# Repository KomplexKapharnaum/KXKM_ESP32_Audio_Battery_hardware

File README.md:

# KXKM_ESP32_Audio_Battery_hardware

## Overview
Hardware workspace for the KXKM ESP32 battery + audio platform.
The repository groups KiCad design files for battery management and remote control boards.

## Installation
Prerequisites:
- KiCad 7/8 for schematic/project edits
- Git LFS is not required for the current tracked files

## Usage
Typical workflow:
1. Open the board project under `Base_board/v3.2/`.
2. Review schematic updates in `*.kicad_sch`.
3. Export manufacturing artifacts (Gerber/BOM) from KiCad when needed.

## Architecture
Main areas:
- `Base_board/`: battery management board revisions
- `Audio_board/`: audio-related board files
- `Remote_control_board/`: remote control board symbols/project config

## Testing & Quality
Recommended checks before commit:
- KiCad ERC/DRC on edited projects
- Diff review on `.kicad_sch`/`.kicad_pro` changes
- Ensure no local artifacts are tracked (`.DS_Store`, `*-backups/*.zip`)

## Performance & Optimization
Optimization focus:
- Keep schematic commits isolated from hygiene/meta commits
- Reduce noisy diffs by excluding generated/local backup files

## Security
Security notes:
- Avoid committing private manufacturing or supplier credentials
- Keep BOM/vendor metadata reviewable in plain text when possible

## Roadmap
Near-term:
- Finalize battery board v3.2 review cycle
- Validate remote control symbol table consistency

<!-- CHANTIER:AUDIT START -->
## Audit & Execution Plan (2026-03-10)

### Snapshot
- Priority: `P2`
- Tech profile: `other`
- Workflows: `yes`
- Tests: `yes`
- Debt markers: `0`
- Source files: `0`

### Corrections Prioritaires
- [ ] Optimisation ciblée perf/maintenabilité
- [ ] Ajouter/fiabiliser les commandes de vérification automatiques.
- [ ] Clore les points bloquants avant optimisation avancée.

### Optimisation
- [ ] Identifier le hotspot principal et mesurer avant/après.
- [ ] Réduire la complexité des modules les plus touchés.

### Mémoire chantier
- Control plane: `/Users/electron/.codex/memories/electron_rare_chantier`
- Repo card: `/Users/electron/.codex/memories/electron_rare_chantier/REPOS/KXKM_ESP32_Audio_Battery_hardware.md`

<!-- CHANTIER:AUDIT END -->

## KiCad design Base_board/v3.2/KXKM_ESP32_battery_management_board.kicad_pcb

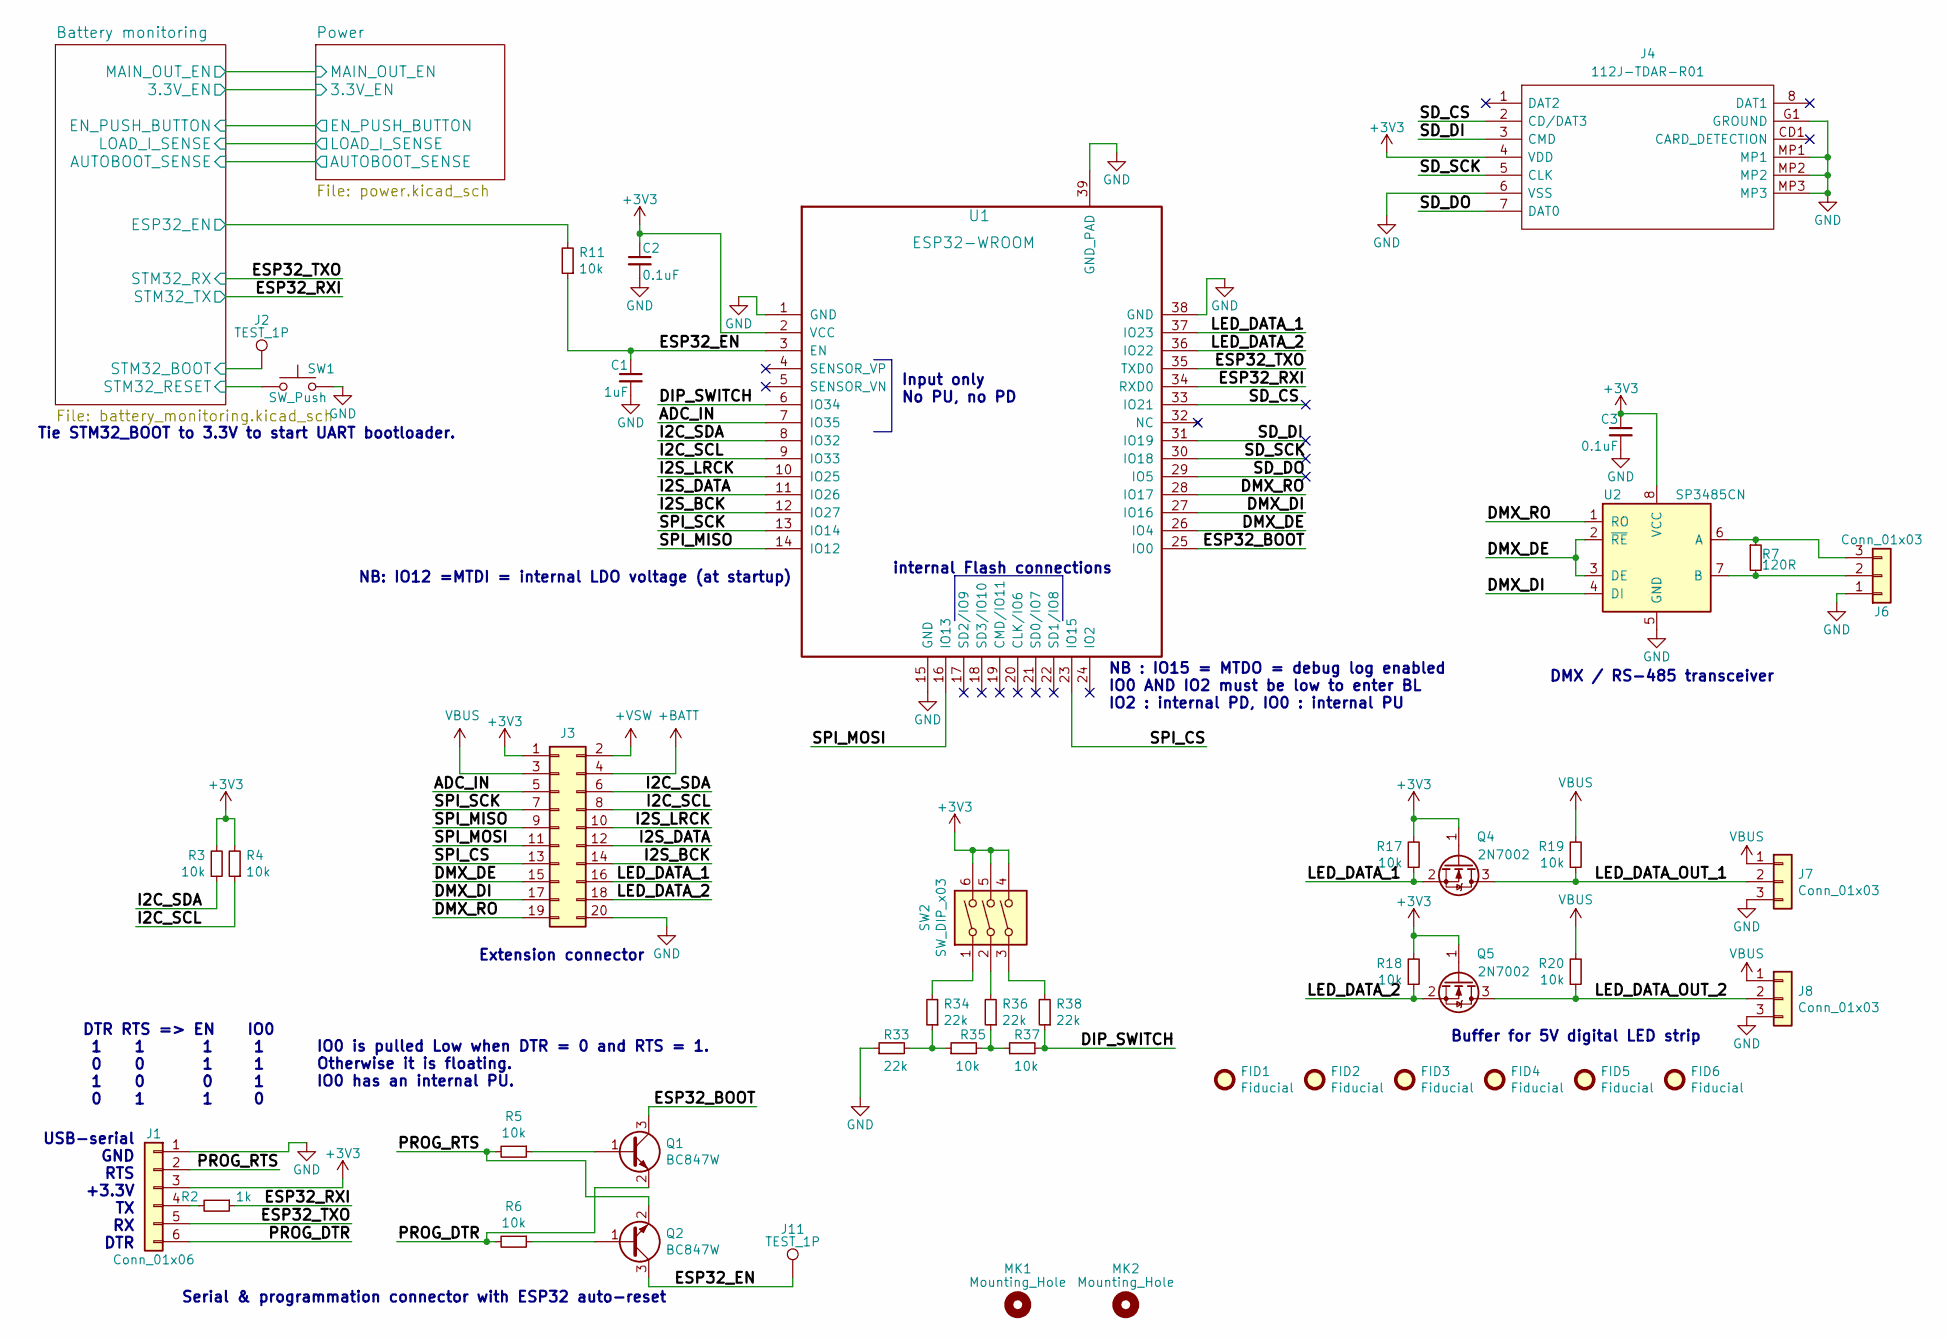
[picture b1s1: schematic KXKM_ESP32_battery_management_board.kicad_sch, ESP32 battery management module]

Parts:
C1: 1uF; C_0603_1608Metric; LCSC C15849
C2, C3: 0.1uF; C_0603_1608Metric; LCSC C14663
FID1, FID2, FID3, FID4, FID5, FID6: Fiducial; Fiducial_0.5mm_Mask1mm
J1: Conn_01x06; PinHeader_1x06_P2.54mm_Vertical
J2, J11: TEST_1P; TestPoint_Pad_D1.5mm
J3: Conn_02x10_Odd_Even; PinSocket_2x10_P2.54mm_Vertical_SMD
J4: 112J-TDAR-R01; 112JTDARR01; Manufacturer_Part_Number 112J-TDAR-R01
J6: Conn_01x03; PinHeader_1x03_P2.54mm_Vertical
J7, J8: Conn_01x03; JST_EH_B3B-EH-A_1x03_P2.50mm_Vertical
MK1, MK2: Mounting_Hole; MountingHole_3.2mm_M3
Q1, Q2: BC847W; SOT-323_SC-70; LCSC C130418
Q4, Q5: 2N7002; SOT-23; LCSC C8545
R2: 1k; R_0603_1608Metric; LCSC C21190
R3, R4, R5, R6, R11, R17, R18, R19, R20, R35, R37: 10k; R_0603_1608Metric; LCSC C25804
R7: 120R; R_0603_1608Metric; LCSC C114681
R33, R34, R36, R38: 22k; R_0603_1608Metric; LCSC C31850
SW1: SW_Push; SW_SPST_KMR2; LCSC C128941
SW2: SW_DIP_x03; SW_DIP_SPSTx03_Piano_CTS_Series194-3MSTN_W7.62mm_P2.54mm; LCSC C319070
U1: ESP32-WROOM; ESP32-WROOM-32U; LCSC C529580
U2: SP3485CN; SOIC-8_3.9x4.9mm_P1.27mm; LCSC C668205

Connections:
+3V3: C2.1, C3.1, J1.3, J3.1, J4.4 (VDD), Q4.1 (G), Q5.1 (G), R3.2, R4.2, R17.2, R18.2, SW2.4, SW2.5, SW2.6, U1.2 (VCC), U2.8 (VCC); also elsewhere on the board
+BATT: J3.4; also elsewhere on the board
+VSW: J3.2; also elsewhere on the board
/ADC_IN: J3.5, U1.7 (IO35)
/Battery monitoring/ESP32_EN: R11.2; also elsewhere on the board
/Battery monitoring/STM32_BOOT: J2.1; also elsewhere on the board
/Battery monitoring/STM32_RST: SW1.1; also elsewhere on the board
/DIP_SWITCH: R37.2, R38.1, U1.6 (IO34)
/DMX_DE: J3.15, U1.26 (IO4), U2.2 (~RE), U2.3 (DE)
/DMX_DI: J3.17, U1.27 (IO16), U2.4 (DI)
/DMX_RO: J3.19, U1.28 (IO17), U2.1 (RO)
/ESP32_BOOT: Q1.3 (C), U1.25 (IO0)
/ESP32_EN: C1.1, J11.1, Q2.3 (C), R11.1, U1.3 (EN)
/ESP32_RXI: R2.1, U1.34 (RXD0); also elsewhere on the board
/ESP32_TXO: J1.5, U1.35 (TXD0); also elsewhere on the board
/I2C_SCL: J3.8, R4.1, U1.9 (IO33)
/I2C_SDA: J3.6, R3.1, U1.8 (IO32)
/I2S_BCK: J3.14, U1.12 (IO27)
/I2S_DATA: J3.12, U1.11 (IO26)
/I2S_LRCK: J3.10, U1.10 (IO25)
/LED_DATA_1: J3.16, Q4.2 (S), R17.1, U1.37 (IO23)
/LED_DATA_2: J3.18, Q5.2 (S), R18.1, U1.36 (IO22)
/LED_DATA_OUT_1: J7.2, Q4.3 (D), R19.1
/LED_DATA_OUT_2: J8.2, Q5.3 (D), R20.1
/PROG_DTR: J1.6, Q1.2 (E), R6.2
/PROG_RTS: J1.2, Q2.2 (E), R5.2
/SD_CS: J4.2 (CD/DAT3), U1.33 (IO21)
/SD_DI: J4.3 (CMD), U1.31 (IO19)
/SD_DO: J4.7 (DAT0), U1.29 (IO5)
/SD_SCK: J4.5 (CLK), U1.30 (IO18)
/SPI_CS: J3.13, U1.23 (IO15)
/SPI_MISO: J3.9, U1.14 (IO12)
/SPI_MOSI: J3.11, U1.16 (IO13)
/SPI_SCK: J3.7, U1.13 (IO14)
GND: C1.2, C2.2, C3.2, J1.1, J3.20, J4.6 (VSS), J4.G1 (GROUND), J4.MP1, J4.MP2, J4.MP3, J6.1, J7.3, J8.3, R33.1, SW1.2, U1.1 (GND), U1.15 (GND), U1.38 (GND), U1.39 (GND_PAD), U2.5 (GND); also elsewhere on the board
unnamed: J1.4, R2.2
unnamed: J6.2, R7.2, U2.7 (B)
unnamed: J6.3, R7.1, U2.6 (A)
unnamed: Q1.1 (B), R5.1
unnamed: Q2.1 (B), R6.1
unnamed: R33.2, R34.1, R35.1
unnamed: R34.2, SW2.1
unnamed: R35.2, R36.1, R37.1
unnamed: R36.2, SW2.2
unnamed: R38.2, SW2.3
VBUS: J3.3, J7.1, J8.1, R19.2, R20.2; also elsewhere on the board

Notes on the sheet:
DMX / RS-485 transceiver
Tie STM32_BOOT to 3.3V to start UART bootloader.
DTR RTS => EN IO0 1 1 1 1 0 0 1 1 1 0 0 1 0 1 1 0
Input only No PU, no PD
Buffer for 5V digital LED strip
USB-serial GND RTS +3.3V TX RX DTR
NB : IO15 = MTDO = debug log enabled IO0 AND IO2 must be low to enter BL IO2 : internal PD, IO0 : internal PU
Serial & programmation connector with ESP32 auto-reset
IO0 is pulled Low when DTR = 0 and RTS = 1. Otherwise it is floating. IO0 has an internal PU.
NB: IO12 =MTDI = internal LDO voltage (at startup)
internal Flash connections
Extension connector

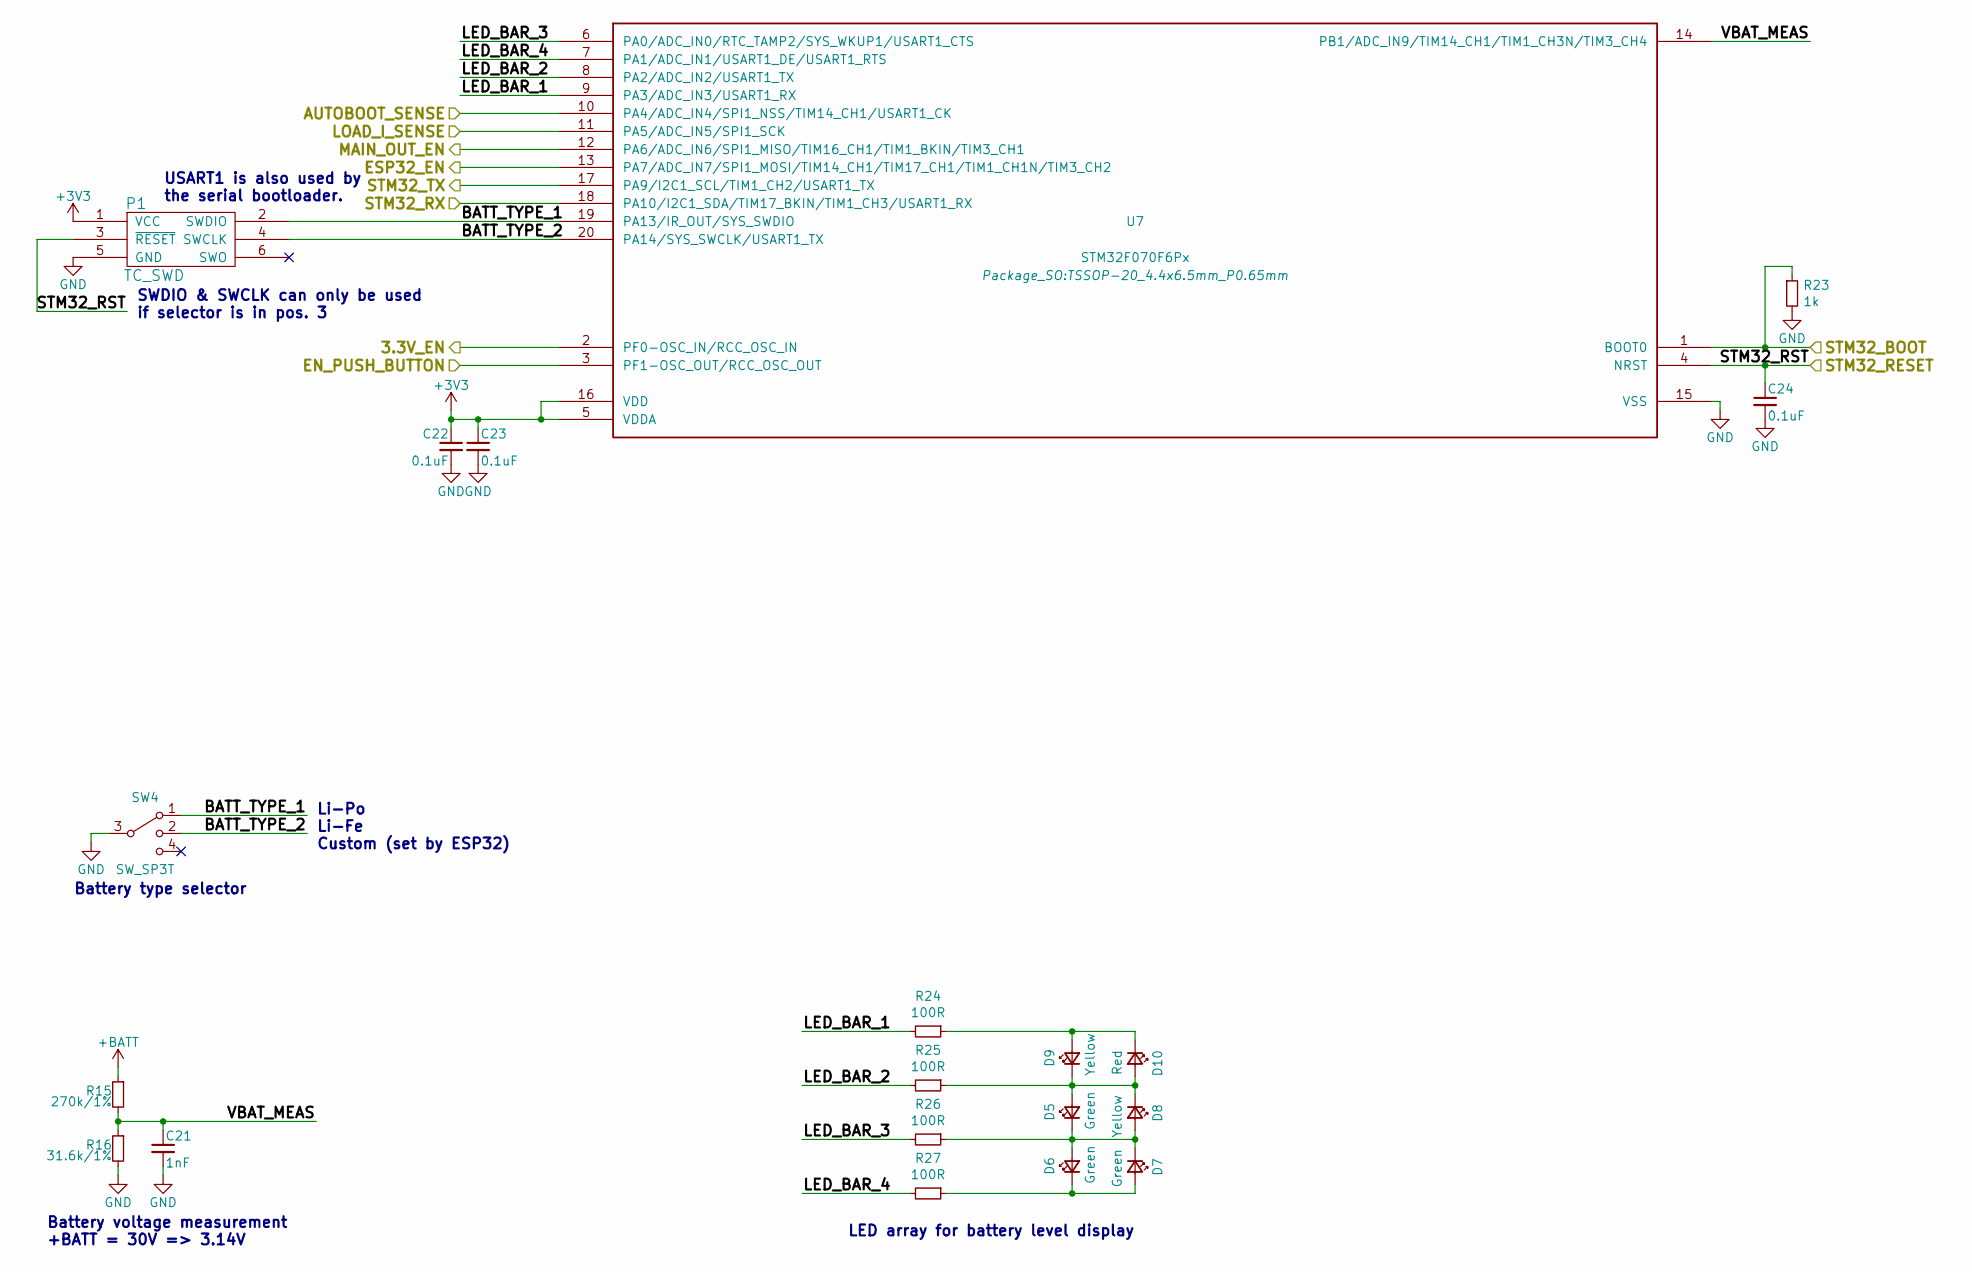
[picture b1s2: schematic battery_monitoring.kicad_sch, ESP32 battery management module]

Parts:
C21: 1nF; C_0603_1608Metric
C22, C23, C24: 0.1uF; C_0603_1608Metric; LCSC C14663
D5, D6, D7: Green; LED_0603_1608Metric; LCSC C72043
D8, D9: Yellow; LED_0603_1608Metric; LCSC C72038
D10: Red; LED_0603_1608Metric; LCSC C2286
P1: TC_SWD; Tag-Connect_TC2030-IDC-NL_2x03_P1.27mm_Vertical
R15: 270k/1%; R_0603_1608Metric; LCSC C22965
R16: 31.6k/1%; R_0603_1608Metric; LCSC C25967
R23: 1k; R_0603_1608Metric; LCSC C21190
R24, R25, R26, R27: 100R; R_0603_1608Metric; LCSC C22775
SW4: SW_SP3T; SW_SP3T_PCM13; LCSC C160878
U7: STM32F070F6Px; TSSOP-20_4.4x6.5mm_P0.65mm; LCSC C86951

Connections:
+3V3: C22.1, C23.1, P1.1 (VCC), U7.5 (VDDA), U7.16 (VDD); also elsewhere on the board
+BATT: R15.1; also elsewhere on the board
/Battery monitoring/3.3V_EN: U7.2 (PF0-OSC_IN/RCC_OSC_IN); also elsewhere on the board
/Battery monitoring/AUTOBOOT_SENSE: U7.10 (PA4/ADC_IN4/SPI1_NSS/TIM14_CH1/USART1_CK); also elsewhere on the board
/Battery monitoring/BATT_TYPE_1: P1.2 (SWDIO), SW4.1, U7.19 (PA13/IR_OUT/SYS_SWDIO)
/Battery monitoring/BATT_TYPE_2: P1.4 (SWCLK), SW4.2, U7.20 (PA14/SYS_SWCLK/USART1_TX)
/Battery monitoring/EN_PUSH_BUTTON: U7.3 (PF1-OSC_OUT/RCC_OSC_OUT); also elsewhere on the board
/Battery monitoring/ESP32_EN: U7.13 (PA7/ADC_IN7/SPI1_MOSI/TIM14_CH1/TIM17_C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); also elsewhere on the board
/Battery monitoring/LED_BAR_1: R24.2, U7.9 (PA3/ADC_IN3/USART1_RX)
/Battery monitoring/LED_BAR_2: R25.2, U7.8 (PA2/ADC_IN2/USART1_TX)
/Battery monitoring/LED_BAR_3: R26.2, U7.6 (PA0/ADC_IN0/RTC_TAMP2/SYS_WKUP1/USART1_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)
/Battery monitoring/LED_BAR_4: R27.2, U7.7 (PA1/ADC_IN1/USART1_DE/USART1_RTS)
/Battery monitoring/LOAD_I_SENSE: U7.11 (PA5/ADC_IN5/SPI1_SCK); also elsewhere on the board
/Battery monitoring/MAIN_OUT_EN: U7.12 (PA6/ADC_IN6/SPI1_MISO/TIM16_CH1/TIM1_BK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); also elsewhere on the board
/Battery monitoring/STM32_BOOT: R23.1, U7.1 (BOOT0); also elsewhere on the board
/Battery monitoring/STM32_RST: C24.1, P1.3 (~RESET), U7.4 (NRST); also elsewhere on the board
/Battery monitoring/VBAT_MEAS: C21.1, R15.2, R16.1, U7.14 (PB1/ADC_IN9/TIM14_CH1/TIM1_CH3N/TIM3_CH4)
/ESP32_RXI: U7.17 (PA9/I2C1_SCL/TIM1_CH2/USART1_TX); also elsewhere on the board
/ESP32_TXO: U7.18 (PA10/I2C1_SDA/TIM17_BKIN/TIM1_CH3/USART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); also elsewhere on the board
GND: C21.2, C22.2, C23.2, C24.2, P1.5 (GND), R16.2, R23.2, SW4.3, U7.15 (VSS); also elsewhere on the board
unnamed: D5.1 (K), D6.2 (A), D7.1 (K), D8.2 (A), R26.1
unnamed: D6.1 (K), D7.2 (A), R27.1
unnamed: D5.2 (A), D8.1 (K), D9.1 (K), D10.2 (A), R25.1
unnamed: D9.2 (A), D10.1 (K), R24.1

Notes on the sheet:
Li-Po Li-Fe Custom (set by ESP32)
Battery type selector
Battery voltage measurement +BATT = 30V => 3.14V
LED array for battery level display
SWDIO & SWCLK can only be used if selector is in pos. 3
USART1 is also used by the serial bootloader.

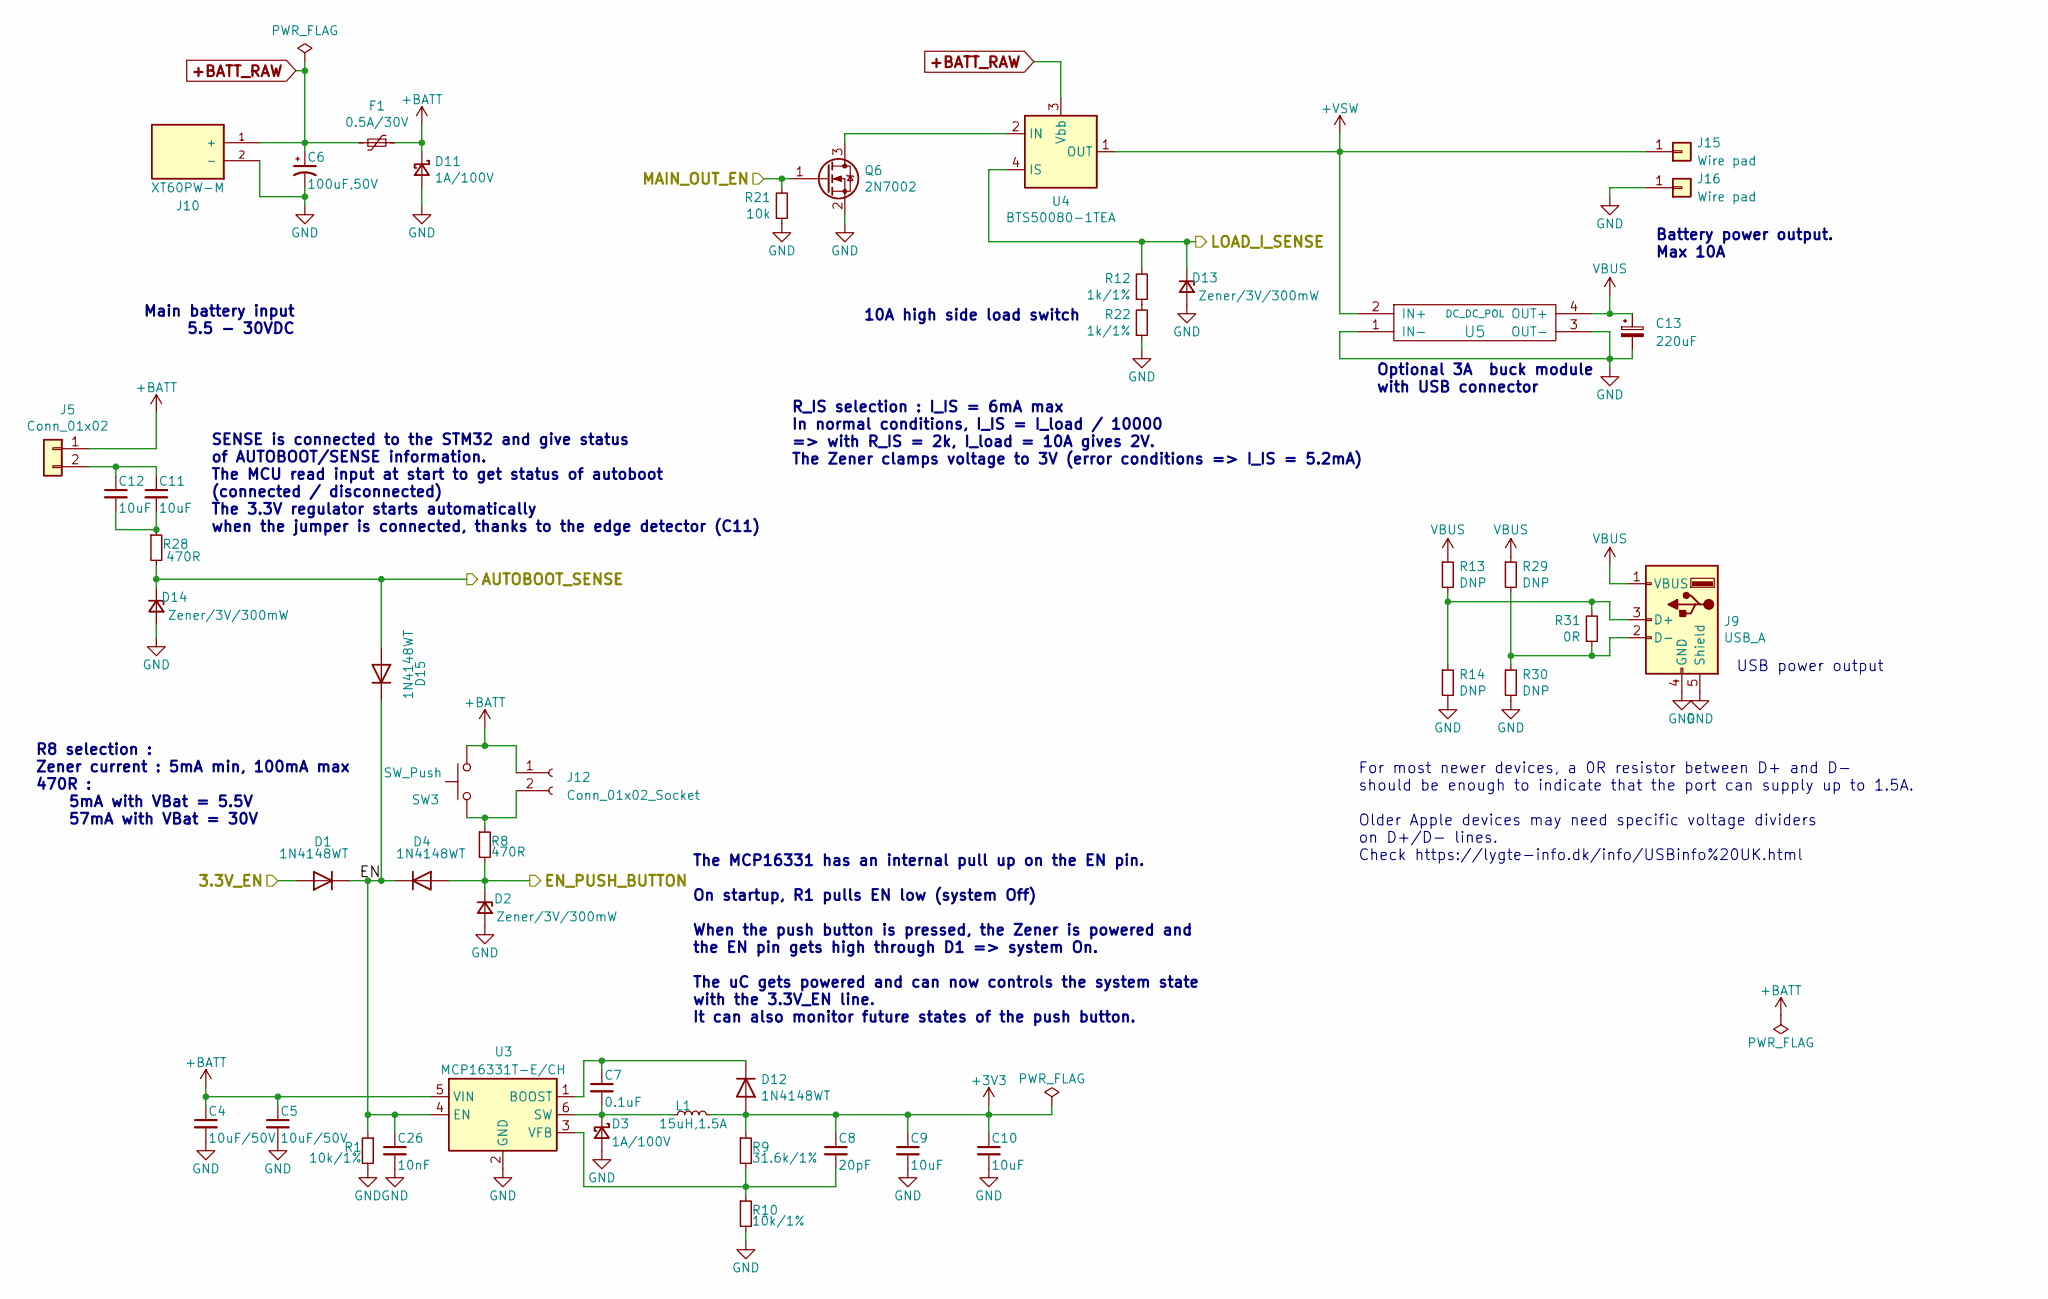
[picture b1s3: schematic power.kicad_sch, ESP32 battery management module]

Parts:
C4, C5: 10uF/50V; C_1206_3216Metric; LCSC C13585
C6: 100uF,50V; CP_Elec_8x10; LCSC C97812
C7: 0.1uF; C_0603_1608Metric; LCSC C14663
C8: 20pF; C_0603_1608Metric; LCSC C1648
C9, C10, C11, C12: 10uF; C_0805_2012Metric
C13: 220uF; CP_Radial_D5.0mm_P2.50mm
C26: 10nF; C_0603_1608Metric; LCSC C57112
D1, D4, D12, D15: 1N4148WT; D_SOD-523; LCSC C68948
D2, D13, D14: Zener/3V/300mW; D_SOD-323; LCSC C19869
D3, D11: 1A/100V; D_SMA; LCSC C14996
F1: 0.5A/30V; Fuse_1812_4532Metric; LCSC C2924945
J5: Conn_01x02; PinHeader_1x02_P2.54mm_Vertical
J9: USB_A; USB_A_Female; LCSC C2345
J10: XT60PW-M; AMASS_XT60PW-M; Manufacturer_Part_Number XT60PW-M
J12: Conn_01x02_Socket; PinHeader_1x02_P2.54mm_Vertical
J15, J16: Wire pad; SolderWirePad_1x01_Drill2mm
L1: 15uH,1.5A; L_Taiyo-Yuden_NR-50xx; LCSC C206232
Q6: 2N7002; SOT-23; LCSC C8545
R1, R10: 10k/1%; R_0603_1608Metric; LCSC C25804
R8, R28: 470R; R_0603_1608Metric; LCSC C23179
R9: 31.6k/1%; R_0603_1608Metric; LCSC C25967
R12, R22: 1k/1%; R_0603_1608Metric; LCSC C21190
R13, R14, R29, R30: DNP; R_0603_1608Metric
R21: 10k; R_0603_1608Metric; LCSC C25804
R31: 0R; R_0603_1608Metric; LCSC C21189
SW3: SW_Push; SW_Tactile_SPST_Angled_PTS645Vx31-2LFS; LCSC C127680
U3: MCP16331T-E/CH; SOT-23-6; LCSC C105695
U4: BTS50080-1TEA; TO-252-4; LCSC C152393
U5: DC_DC_POL; DC_DC_Buck_module_22x17mm

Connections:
+3V3: C8.1, C9.1, C10.1, D12.2 (A), L1.2, R9.1; also elsewhere on the board
+BATT: C4.1, C5.1, D11.1 (K), F1.1, J5.1, J12.1, SW3.2, U3.5 (VIN); also elsewhere on the board
+BATT_RAW: C6.1, F1.2, J10.1 (+), U4.3 (Vbb)
+VSW: J15.1, U4.1 (OUT), U4.5 (OUT), U5.2 (IN+); also elsewhere on the board
/Battery monitoring/3.3V_EN: D1.2 (A); also elsewhere on the board
/Battery monitoring/AUTOBOOT_SENSE: D14.1 (K), D15.2 (A), R28.2; also elsewhere on the board
/Battery monitoring/EN_PUSH_BUTTON: D2.1 (K), D4.2 (A), R8.2; also elsewhere on the board
/Battery monitoring/LOAD_I_SENSE: D13.1 (K), R12.2, U4.4 (IS); also elsewhere on the board
/Battery monitoring/MAIN_OUT_EN: Q6.1 (G), R21.2; also elsewhere on the board
/Power/EN: C26.1, D1.1 (K), D4.1 (K), D15.1 (K), R1.1, U3.4 (EN)
GND: C4.2, C5.2, C6.2, C9.2, C10.2, C13.2, C26.2, D2.2 (A), D3.2 (A), D11.2 (A), D13.2 (A), D14.2 (A), J9.4 (GND), J9.5 (Shield), J10.2 (-), J16.1, Q6.2 (S), R1.2, R10.2, R14.2, R21.1, R22.1, R30.2, SW3.3, SW3.4, U3.2 (GND), U5.1 (IN-), U5.3 (OUT-); also elsewhere on the board
unnamed: C11.2, C12.2, R28.1
unnamed: C7.2, D3.1 (K), L1.1, U3.6 (SW)
unnamed: C7.1, D12.1 (K), U3.1 (BOOST)
unnamed: C11.1, C12.1, J5.2
unnamed: J9.3 (D+), R13.2, R14.1, R31.2
unnamed: J9.2 (D-), R29.2, R30.1, R31.1
unnamed: J12.2, R8.1, SW3.1
unnamed: Q6.3 (D), U4.2 (IN)
unnamed: R12.1, R22.2
unnamed: C8.2, R9.2, R10.1, U3.3 (VFB)
VBUS: C13.1, J9.1 (VBUS), R13.1, R29.1, U5.4 (OUT+); also elsewhere on the board

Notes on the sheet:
R8 selection : Zener current : 5mA min, 100mA max 470R : 5mA with VBat = 5.5V 57mA with VBat = 30V
For most newer devices, a 0R resistor between D+ and D- should be enough to indicate that the port can supply up to 1.5A. Older Apple devices may need specific voltage dividers on D+/D- lines. Check https://lygte-info.dk/info/USBinfo%20UK.html
R_IS selection : I_IS = 6mA max In normal conditions, I_IS = I_load / 10000 => with R_IS = 2k, I_load = 10A gives 2V. The Zener clamps voltage to 3V (error conditions => I_IS = 5.2mA)
The MCP16331 has an internal pull up on the EN pin. On startup, R1 pulls EN low (system Off) When the push button is pressed, the Zener is powered and the EN pin gets high through D1 => system On. The uC gets powered and can now controls the system state with the 3.3V_EN line. It can also monitor f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
10A high side load switch
USB power output
SENSE is connected to the STM32 and give status of AUTOBOOT/SENSE information. The MCU read input at start to get status of autoboot (connected / disconnected) The 3.3V regulator starts automatically when the jumper is connected, thanks to the edge detector (C11)
Optional 3A buck module with USB connector
Main battery input 5.5 - 30VDC
Battery power output. Max 10A

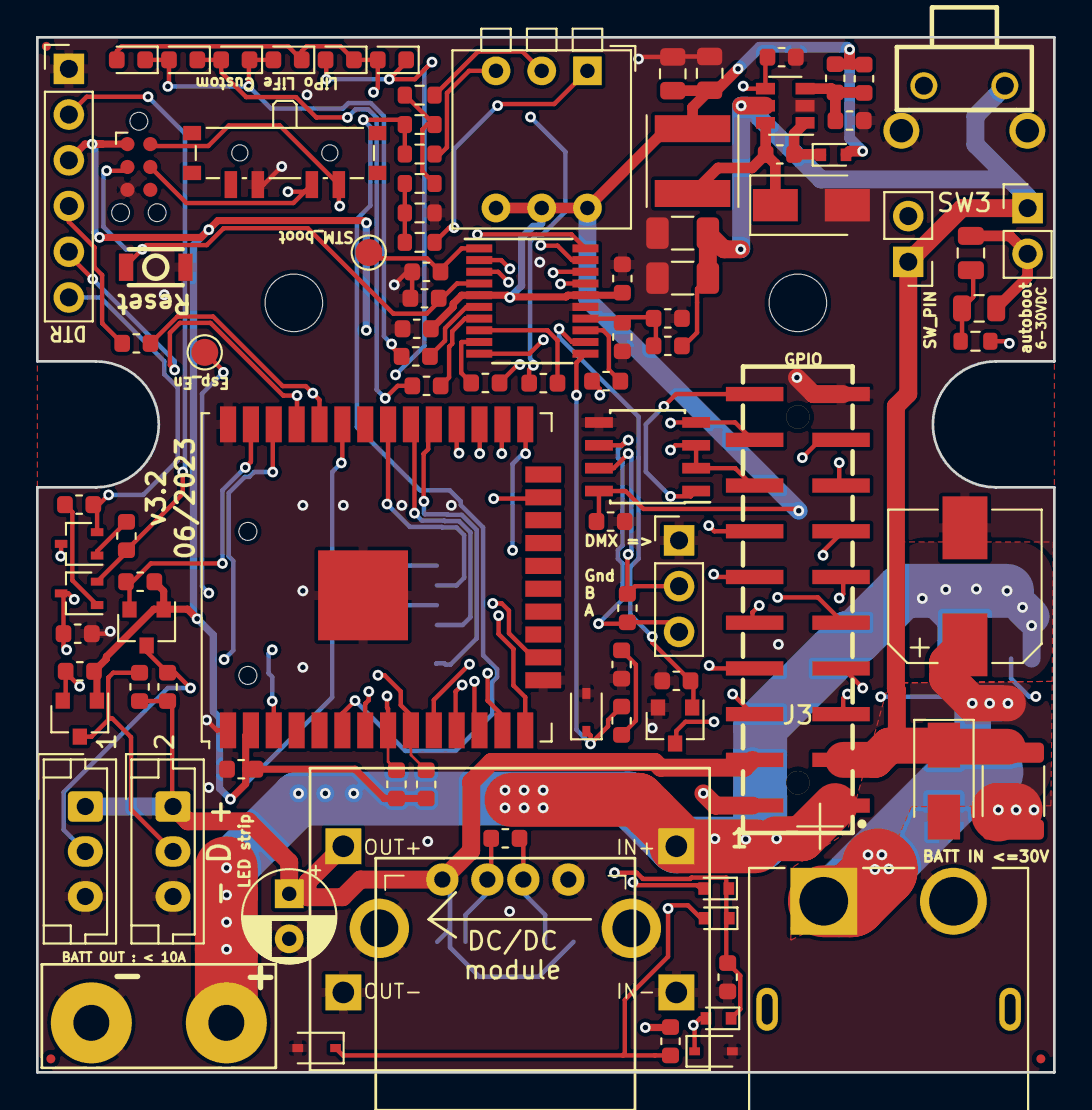
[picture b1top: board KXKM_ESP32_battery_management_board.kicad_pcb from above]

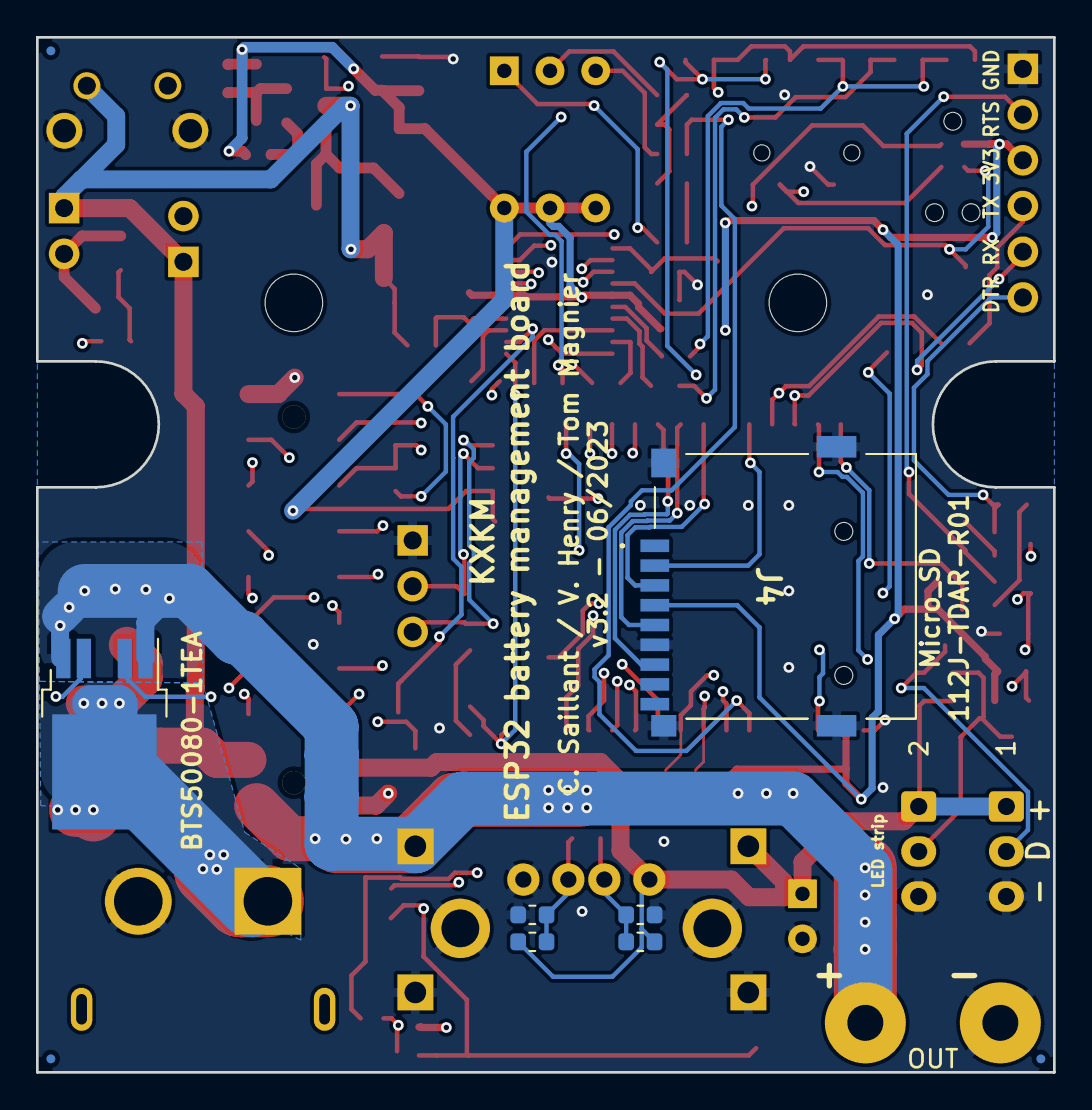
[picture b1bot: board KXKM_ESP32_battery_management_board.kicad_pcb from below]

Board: 4 copper layers, 56.5 x 57.5 mm, 110 parts (9 on the bottom side), 74 nets.

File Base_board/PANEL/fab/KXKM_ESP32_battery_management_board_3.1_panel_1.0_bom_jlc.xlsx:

Comment | Designator | Footprint | JLCPCB Part
BC847W | B2-Q2,B4-Q1,B8-Q1,B5-Q2,B3-Q1,B7-Q2,B1-Q2,B4-Q2,B6-Q2,B0-Q2,B1-Q1,B8-Q2,B2-Q1,B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 | SOT-323_SC-70 | C75568
SW_SP3T | B1-SW4,B4-SW4,B7-SW4,B2-SW4,B5-SW4,B6-SW4,B0-SW4,B3-SW4,B8-SW4 | SW_SP3T_PCM13 | C160878
Conn_02x10_Odd_Even | B7-J3,B5-J3,B4-J3,B0-J3,B1-J3,B6-J3,B2-J3,B3-J3,B8-J3 | PinSocket_2x10_P2.54mm_Vertical_SMD | C59981
Green | B2-D7,B0-D7,B2-D5,B3-D5,B3-D6,B1-D5,B2-D6,B5-D5,B4-D6,B0-D6,B7-D5,B8-D7,B8-D5,B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 | LED_0603_1608Metric | C72043
470R | B1-R28,B4-R8,B4-R28,B6-R8,B3-R8,B5-R8,B8-R8,B0-R8,B1-R8,B7-R8,B2-R8,B8-R28,B6-R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 | R_0603_1608Metric | C23179
10k | B2-R3,B8-R3,B1-R19,B5-R6,B5-R37,B5-R18,B6-R6,B8-R6,B6-R17,B1-R20,B6-R11,B6-R35,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 | R_0603_1608Metric | C25804
100uF,50V | B7-C6,B2-C6,B0-C6,B1-C6,B3-C6,B4-C6,B8-C6,B6-C6,B5-C6 | CP_Elec_8x10 | C97812
SW_Push | B4-SW1,B0-SW1,B7-SW1,B1-SW1,B6-SW1,B3-SW1,B2-SW1,B5-SW1,B8-SW1 | SW_SPST_KMR2 | C128941
0R | B5-R31,B6-R31,B7-R31,B8-R31,B2-R31,B3-R31,B1-R31,B4-R31,B0-R31 | R_0603_1608Metric | C21189
1k | B6-R23,B7-R23,B5-R2,B6-R2,B3-R2,B3-R23,B2-R23,B2-R2,B7-R2,B8-R2,B8-R23,B0-R23,B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 | R_0603_1608Metric | C21190
22k | B2-R38,B1-R33,B8-R38,B3-R36,B1-R38,B5-R33,B0-R38,B0-R33,B8-R33,B3-R33,B4-R38,B1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 | R_0603_1608Metric | C31850
Yellow | B8-D8,B6-D8,B1-D9,B7-D9,B8-D9,B2-D8,B1-D8,B0-D8,B3-D9,B2-D9,B5-D9,B6-D9,B0-D9,B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 | LED_0603_1608Metric | C72038
MCP16331T-E/CH | B3-U3,B7-U3,B1-U3,B8-U3,B2-U3,B0-U3,B4-U3,B6-U3,B5-U3 | SOT-23-6 | C105695
SW_DIP_x03 | B7-SW2,B6-SW2,B0-SW2,B5-SW2,B4-SW2,B1-SW2,B2-SW2,B3-SW2,B8-SW2 | SW_DIP_SPSTx03_Piano_CTS_Series194-3MSTN_W7.62mm_P2.54mm | C319070
31.6k/1% | B6-R16,B0-R16,B4-R16,B3-R16,B1-R16,B1-R9,B4-R9,B8-R16,B5-R16,B6-R9,B5-R9,B7-R9,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 | R_0603_1608Metric | C25967
Conn_01x02 | B0-J5,B8-J5,B4-J5,B1-J5,B5-J5,B6-J5,B3-J5,B2-J5,B7-J5 | PinHeader_1x02_P2.54mm_Vertical | C124375
1nF | B6-C21,B5-C21,B2-C21,B1-C21,B7-C21,B3-C21,B0-C21,B8-C21,B4-C21 | C_0603_1608Metric | C1588
10k/1% | B5-R1,B8-R1,B5-R10,B2-R10,B3-R10,B6-R10,B0-R1,B7-R10,B0-R10,B6-R1,B4-R10,B4-R1,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 | R_0603_1608Metric | C25804
15uH,1.5A | B3-L1,B4-L1,B1-L1,B7-L1,B8-L1,B5-L1,B6-L1,B0-L1,B2-L1 | L_Taiyo-Yuden_NR-50xx | C206232
10uF/50V | B5-C4,B8-C4,B3-C5,B2-C4,B2-C5,B4-C5,B0-C5,B0-C4,B7-C5,B5-C5,B4-C4,B7-C4,B6-C5,B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 | C_1206_3216Metric | C13585
0.5A/30V | B8-F1,B2-F1,B7-F1,B5-F1,B0-F1,B3-F1,B6-F1,B4-F1,B1-F1 | Fuse_1812_4532Metric | C269128
270k/1% | B7-R15,B6-R15,B2-R15,B5-R15,B1-R15,B0-R15,B3-R15,B4-R15,B8-R15 | R_0603_1608Metric | C22965
10uF | B6-C9,B5-C9,B2-C9,B4-C10,B7-C10,B1-C10,B0-C9,B8-C10,B3-C10,B2-C10,B8-C9,B6-C10,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 | C_0805_2012Metric | C440198
Conn_01x06 | B1-J1,B8-J1,B5-J1,B6-J1,B2-J1,B4-J1,B0-J1,B7-J1,B3-J1 | PinHeader_1x06_P2.54mm_Vertical | C37208
1N4148WT | B5-D1,B4-D12,B7-D15,B8-D1,B0-D1,B2-D15,B0-D4,B4-D4,B8-D12,B5-D4,B1-D15,B3-D1,B3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 | D_SOD-523 | C68948
0.1uF | B4-C2,B1-C7,B0-C22,B8-C23,B5-C23,B4-C7,B2-C2,B5-C22,B1-C23,B1-C24,B2-C7,B5-C2,B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 | C_0603_1608Metric | C14663
10nF | B1-C26,B0-C26,B3-C26,B2-C26,B6-C26,B7-C26,B5-C26,B8-C26,B4-C26 | C_0603_1608Metric | C57112
1uF | B1-C1,B0-C1,B5-C1,B8-C11,B4-C1,B3-C1,B2-C11,B8-C1,B6-C11,B4-C11,B7-C11,B2-C1,B7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 | C_0603_1608Metric | C15849
1A/100V | B4-D11,B0-D11,B3-D11,B4-D3,B3-D3,B6-D11,B1-D11,B0-D3,B2-D11,B5-D11,B1-D3,B2-D3,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 | D_SMA | C14996
SW_Push | B8-SW3,B5-SW3,B4-SW3,B7-SW3,B0-SW3,B2-SW3,B1-SW3,B3-SW3,B6-SW3 | SW_Tactile_SPST_Angled_PTS645Vx58-2LFS_horiz_pads | C127680
USB_A | B7-J9,B6-J9,B0-J9,B2-J9,B1-J9,B3-J9,B8-J9,B4-J9,B5-J9 | USB_A_Female | C2345
20pF | B6-C8,B2-C8,B1-C8,B5-C8,B8-C8,B3-C8,B4-C8,B0-C8,B7-C8 | C_0603_1608Metric | C1648
2N7002 | B5-Q5,B3-Q6,B5-Q4,B7-Q6,B1-Q6,B4-Q5,B1-Q4,B3-Q5,B5-Q6,B2-Q4,B6-Q5,B8-Q4,B7-Q4,B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 | SOT-23 | C8545
ESP32-WROOM | B8-U1,B4-U1,B3-U1,B5-U1,B2-U1,B1-U1,B7-U1,B6-U1,B0-U1 | ESP32-WROOM-32U | C328062
1k/1% | B6-R22,B1-R12,B5-R12,B2-R22,B0-R22,B8-R22,B3-R12,B4-R22,B1-R22,B3-R22,B5-R22,B7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 | R_0603_1608Metric | C21190
Zener/3V/300mW | B1-D13,B2-D13,B3-D14,B1-D2,B6-D14,B3-D13,B8-D14,B7-D2,B8-D13,B0-D13,B7-D13,B8-D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 | D_SOD-323 | C19869
SP3485EEN | B8-U2,B5-U2,B2-U2,B1-U2,B3-U2,B4-U2,B0-U2,B6-U2,B7-U2 | SOIC-8_3.9x4.9mm_P1.27mm | C668205
100R | B8-R25,B2-R27,B4-R24,B5-R27,B1-R27,B6-R26,B3-R24,B2-R26,B7-R25,B5-R24,B6-R25,B3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 | R_0603_1608Metric | C22775
47k | B1-R32,B0-R32,B6-R32,B8-R32,B4-R32,B2-R32,B7-R32,B5-R32,B3-R32 | R_0603_1608Metric | C25819
STM32F070F6P6 | B7-U7,B0-U7,B6-U7,B2-U7,B4-U7,B3-U7,B1-U7,B8-U7,B5-U7 | TSSOP-20_4.4x6.5mm_P0.65mm | C86951
Conn_01x04 | B8-J4,B4-J4,B1-J4,B0-J4,B2-J4,B7-J4,B6-J4,B5-J4,B3-J4 | PinSocket_1x04_P2.54mm_Vertical | C124378
BTS50080-1TEA | B4-U4,B5-U4,B0-U4,B3-U4,B8-U4,B6-U4,B1-U4,B2-U4,B7-U4 | TO-252-4 | C152393
120R | B1-R7,B8-R7,B7-R7,B4-R7,B2-R7,B3-R7,B5-R7,B0-R7,B6-R7 | R_0603_1608Metric | C114681
Conn_01x03 | B0-J6,B8-J6,B7-J6,B5-J6,B4-J6,B6-J6,B1-J6,B3-J6,B2-J6 | PinHeader_1x03_P2.54mm_Vertical | C429954
Red | B8-D10,B1-D10,B3-D10,B5-D10,B0-D10,B2-D10,B4-D10,B7-D10,B6-D10 | LED_0603_1608Metric | C2286

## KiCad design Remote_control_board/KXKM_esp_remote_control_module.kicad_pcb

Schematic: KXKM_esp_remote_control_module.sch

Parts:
C1, C3: 47n; C_Disc_D4.3mm_W1.9mm_P5.00mm
C2: 4.7n; C_Disc_D4.3mm_W1.9mm_P5.00mm
C4: 0.1u; C_Disc_D3.0mm_W1.6mm_P2.50mm
C5: 0.33u; C_Disc_D4.3mm_W1.9mm_P5.00mm
D1: LED; LED_0805_2012Metric_Pad1.15x1.40mm_HandSolder
D2: DIODE; D_0805_2012Metric_Pad1.15x1.40mm_HandSolder
J1, J6: Conn_01x03; PinHeader_1x03_P2.54mm_Vertical
J2: Conn_02x10_Odd_Even; PinHeader_2x10_P2.54mm_Vertical_SMD
J3: Conn_02x10_Odd_Even; PinSocket_2x10_P2.54mm_Vertical_SMD
J4: GPIOB_conn; PinHeader_1x10_P2.54mm_Vertical
J5: GPIOA_conn; PinHeader_1x10_P2.54mm_Vertical
JP1, JP2: Solder_Open; SolderJumper-2_P1.3mm_Open_TrianglePad1.0x1.5mm
R1: 22k; R_Axial_DIN0204_L3.6mm_D1.6mm_P5.08mm_Horizontal
R2: 220; R_0805_2012Metric_Pad1.15x1.40mm_HandSolder
SW1: SW_SPDT; Sw_MFS101D-10_1x03_P2.00mm
SW2: SW_Push; SW_Tactile_SPST_Angled_PTS645Vx58-2LFS
U1: HO10P-P-SP33; HO10PSP33
U3: MCP23017_SP; DIP-28_W7.62mm
U4: L78L33_TO92; TO-92_Inline

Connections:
+3V3: D2.2, J1.1, J2.1, J3.1, J4.10, J5.10, U3.9, U3.18
+BATT: J2.4, J3.4, JP1.1, SW1.2
+VSW: J2.2, J3.2
/A0: J5.9, U3.21
/A1: J5.8, U3.22
/A2: J5.7, U3.23
/A3: J5.6, U3.24
/A4: J5.5, U3.25
/A5: J5.4, U3.26
/A6: J5.3, U3.27
/A7: SW2.1, U3.28
/ADC: J2.5, J3.5, JP2.2
/B0: J4.9, U3.1
/B1: J4.8, U3.2
/B2: J4.7, U3.3
/B3: J4.6, U3.4
/B4: J4.5, U3.5
/B5: J4.4, U3.6
/B6: J4.3, U3.7
/B7: R2.2, U3.8
/DMX_DE: J2.15, J3.15
/DMX_DI: J2.17, J3.17
/DMX_RO: J2.19, J3.19
/I2C_SCL: J2.8, J3.8, U3.12
/I2C_SDA: J2.6, J3.6, U3.13
/I2S_BCK: J2.14, J3.14
/I2S_DATA: J2.12, J3.12
/I2S_LRCK: J2.10, J3.10
/LED_D1: J2.16, J3.16
/LED_D2: J2.18, J3.18
/SPI_CS: J2.13, J3.13
/SPI_MISO: J2.9, J3.9
/SPI_MOSI: J2.11, J3.11
/SPI_SCK: J2.7, J3.7
/ext_3.3: C1.1, C3.1, J6.1, R1.1, U1.1
/ext_gnd: C1.2, C2.1, J6.2, U1.2
/ho10_out: C2.2, J6.3, U1.3
GND: C4.2, C5.2, D1.1, J1.2, J2.20, J3.20, J4.1, J5.1, SW2.2, U3.10, U3.15, U3.16, U3.17, U4.2 (GND)
unnamed: C3.2, U1.4
unnamed: C4.1, D2.1, U4.1 (VO)
unnamed: C5.1, JP1.2, SW1.1, U4.3 (VI)
unnamed: D1.2, R2.1
unnamed: J1.3, JP2.1
unnamed: R1.2, U1.5
VBUS: J2.3, J3.3, J4.2, J5.2

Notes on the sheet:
ESP32 board extension connector
Optional extension connector pass through
Address = Zero
2 GPIO saved for on board modules
